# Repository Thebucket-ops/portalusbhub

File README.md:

# ***PortalHub***

This is a USB hub that lets you connect 4 USBs inspired by portal

The repository is structured as follows:

 - CAD: with the models for the casing of the hub in various formats
 - PCB: with the schematics for the pcb in epro and kicad + gerber

## PCB
Here is the pcb plus its schematic:

## BOM
The BOM is as follows:
* 4 usb-A 2.0 connectors
* 1 usb-c connector
* 1 CoreChips SL2.1s
* 2 resistors 5.1k
* 8 condensers 1uF
* 3 condensers 100nF

## CASE
And here's the case i made for the hub, it has a top side and a bottom one:

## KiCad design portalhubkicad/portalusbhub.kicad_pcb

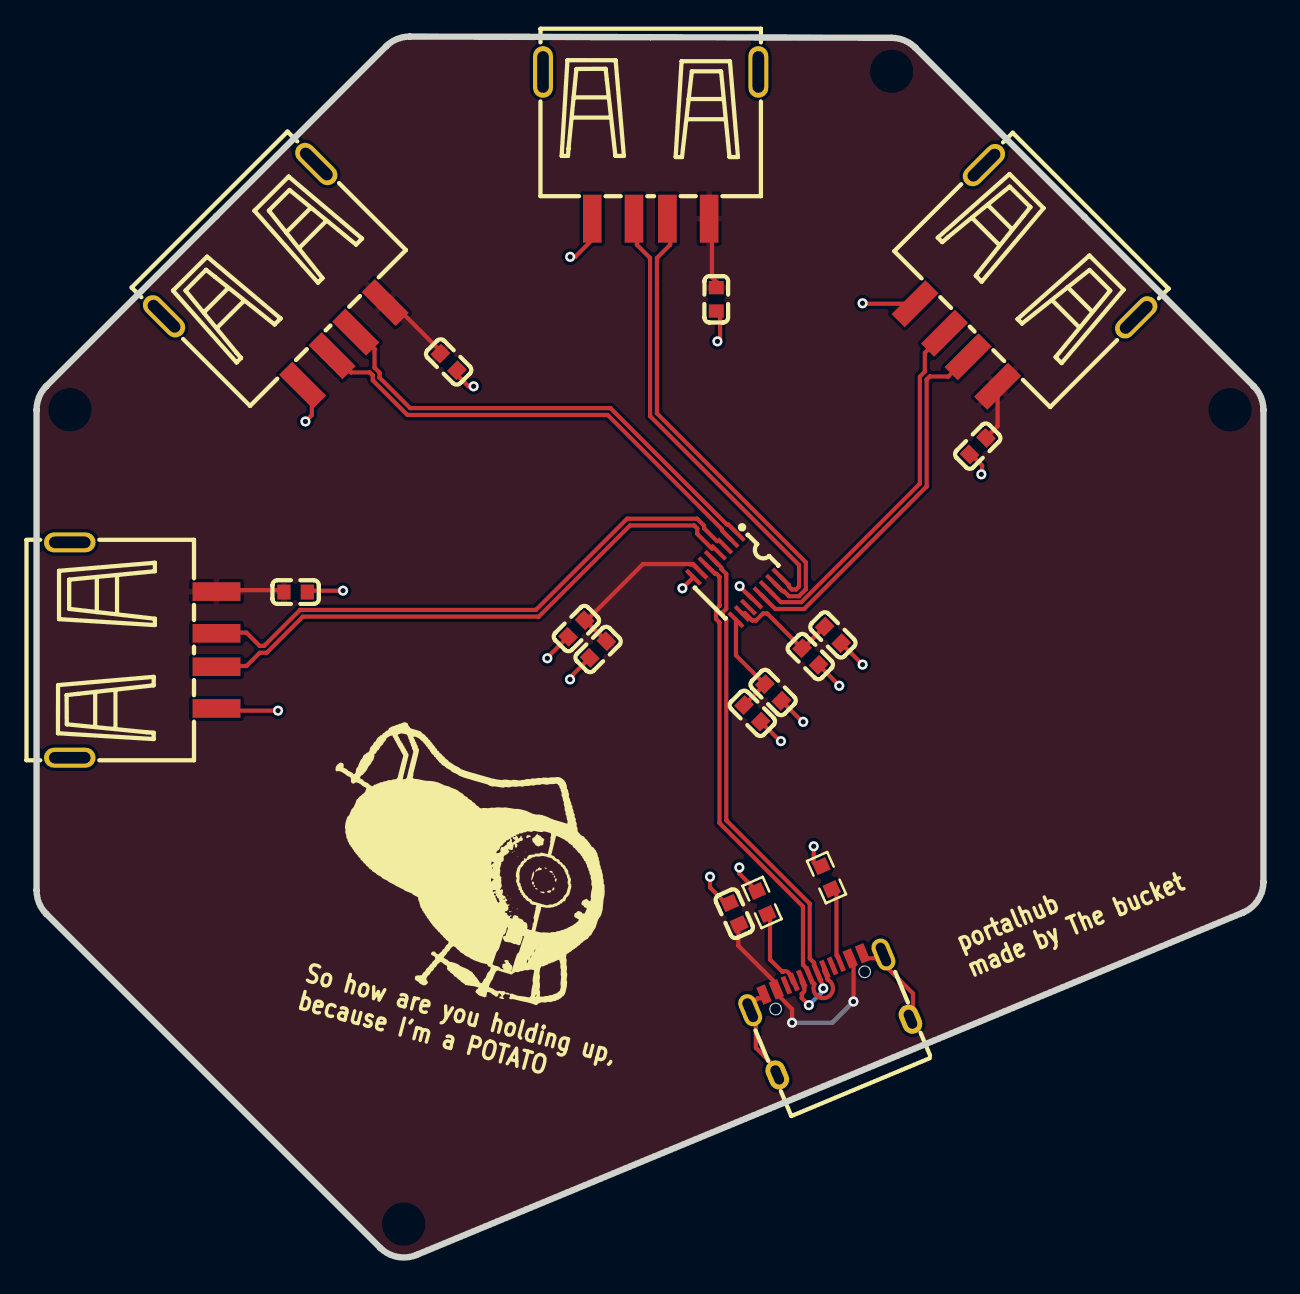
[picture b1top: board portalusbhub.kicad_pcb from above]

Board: 2 copper layers, 73.5 x 73.1 mm, 19 parts (0 on the bottom side), 16 nets.

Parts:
C1, C2, C3, C4, C5, C6, C7, C8, C9, C10: C0603
CIN: C0603
R1, R2: R0603
U1: SSOP-16_L4.6-W2.6-P0.53-LS4.0-BL
USB1, USB2, USB3, USB4: USB-A-TH_10.0QHHTZB6.3
USBIN: USB-C-SMD_TYPE-C-16PIN-2MD-073

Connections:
$1N1063: R2.2, USBIN.B5
$1N1068: R1.2, USBIN.A5
$1N2091: C7.1, C8.1, U1.9
$1N2107: C9.1, C10.1, U1.10
+5V: C1.1, C2.1, C3.1, C4.1, C5.1, C6.1, CIN.1, U1.7, USB1.1, USB2.1, USB3.1, USB4.1, USBIN.A4B9, USBIN.B4A9
DN: U1.5, USBIN.A7, USBIN.B7
DN1: U1.3, USB1.2
DN2: U1.1, USB2.2
DN3: U1.15, USB3.2
DN4: U1.13, USB4.2
DP: U1.6, USBIN.A6, USBIN.B6
DP1: U1.4, USB1.3
DP2: U1.2, USB2.3
DP3: U1.16, USB3.3
DP4: U1.14, USB4.3
GND: C1.2, C2.2, C3.2, C4.2, C5.2, C6.2, C7.2, C8.2, C9.2, C10.2, CIN.2, R1.1, R2.1, U1.8, U1.12, USB1.4, USB1.5, USB1.6, USB2.4, USB2.5, USB2.6, USB3.4, USB3.5, USB3.6, USB4.4, USB4.5, USB4.6, USBIN.13, USBIN.14, USBIN.A1B12, USBIN.B1A12

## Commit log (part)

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2026-06-01 added the files for the pcb
2026-06-02 updated pcb and reuploaded
2026-06-04 updated everything
2026-06-06 added render
2026-06-12 Create LICENSE
2026-06-19 reworking things
2026-06-20 Added render, updated case files and pcb files
2026-06-21 updated render image
